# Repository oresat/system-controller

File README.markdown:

# OreSat "System Controller" Board 

## Overview

TBD

## Description

TBD

## Notes

TBD

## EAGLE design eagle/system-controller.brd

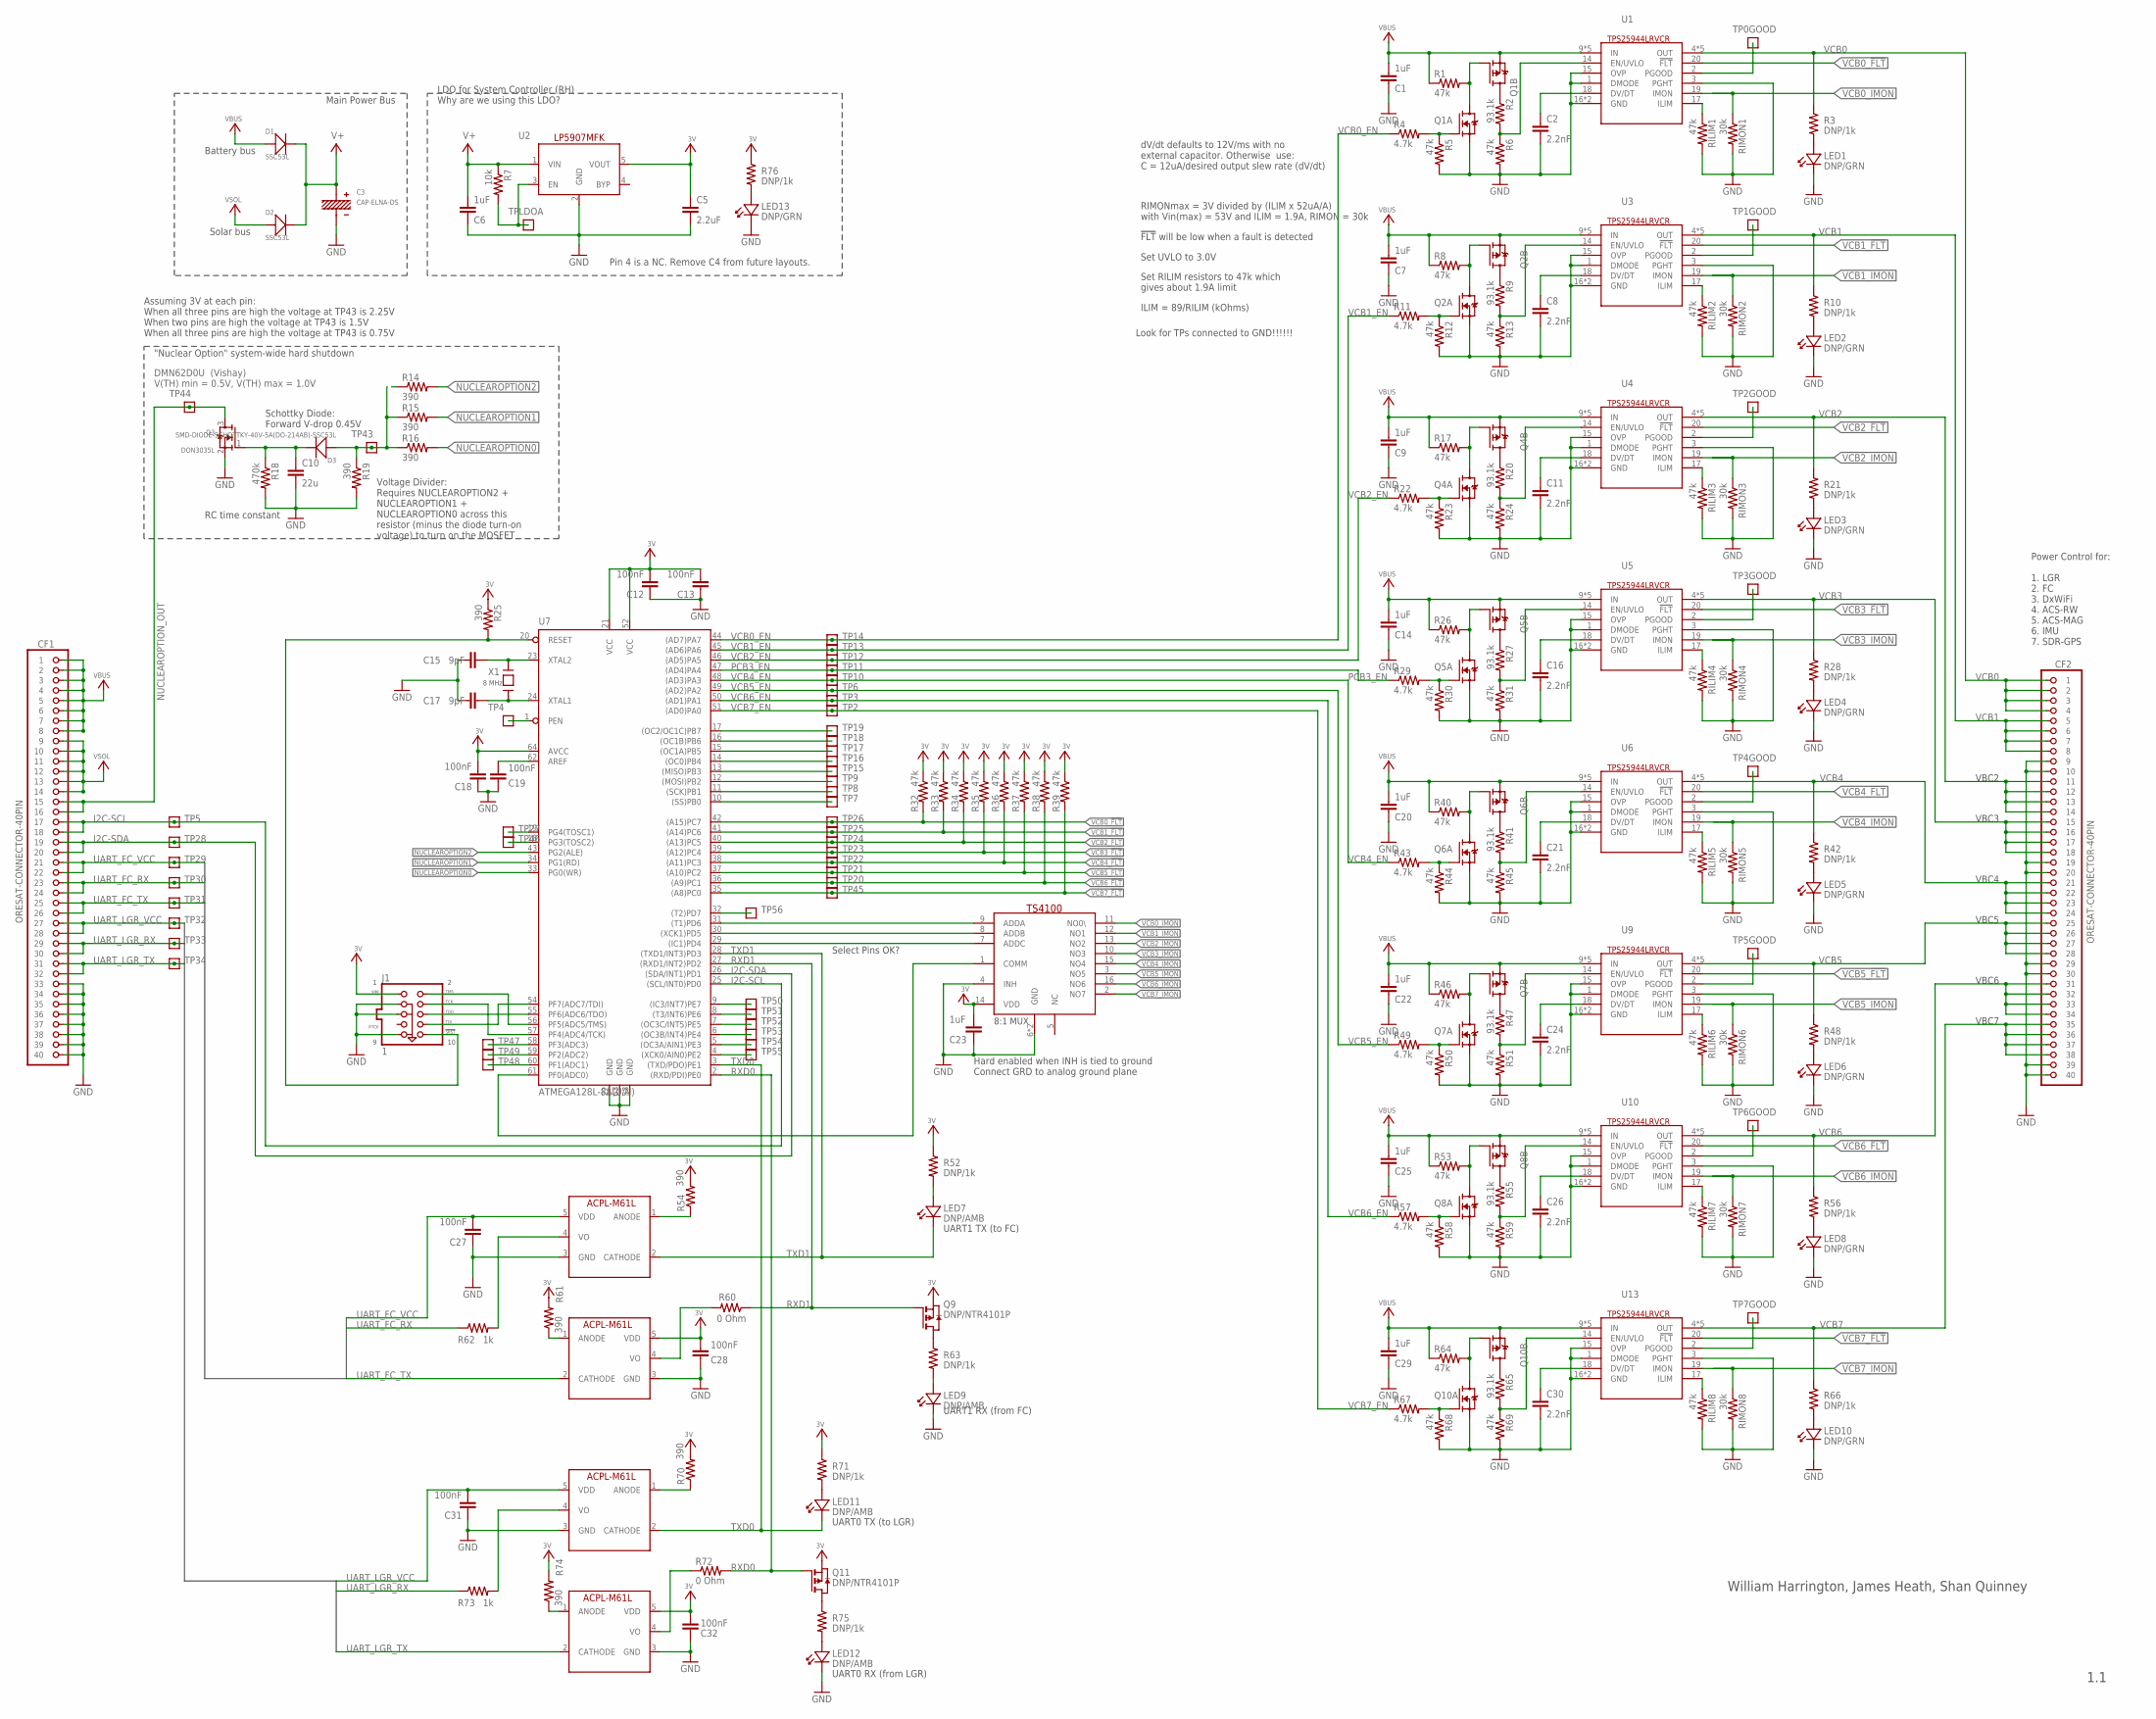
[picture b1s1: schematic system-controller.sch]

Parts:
C1, C6, C7, C9, C14, C20, C22, C23, C25, C29: 1uF; .0603-B-NOSILK; MPN CL10B105KP8NNNC
C2, C8, C11, C16, C21, C24, C26, C30: 2.2nF; .0603-B-NOSILK; MPN CL10C222GA8NNNC
C3: CAP-ELNA-DS; CAP-ELNA-DS-SERIES; MPN DSK-3R3H224U-HL
C5: 2.2uF; .0603-B-NOSILK; MPN CL10A225KQ8NNNC
C10: 22u; .0603-B-NOSILK; MPN C0603C103J5RACTU
C12, C13, C18, C19, C27, C28: 100nF; .0603-B-NOSILK; MPN C0603C104J4RACTU
C15, C17: 9pF; .0603-B-NOSILK; MPN CBR02C909B5GAC
C31, C32: 100nF; .0603-B-NOSILK; MPN GRM155R71C104JA88D
CF1, CF2: ORESAT-CONNECTOR-40PIN; HARWIN-ARCHER-M50-3202045; MPN M50-3202045
D1, D2: SSC53L; DO-214AB; MPN SSC53L-E3/57T
D3: SMD-DIODE-SCHOTTKY-40V-5A(DO-214AB)-SSC53L; DO-214AB; MPN SSC53L-E3/57T
J1: 1; PINHEADER-2X5-0.05+POL+SILK; MPN 3220-10-0100-00
LED1, LED2, LED3, LED4, LED5, LED6, LED8, LED10, LED13: DNP/GRN; LED-0603; MPN 150060GS75000
LED7, LED9, LED11, LED12: DNP/AMB; LED-0603; MPN LA L296-Q2R2-1-Z
Q1, Q2, Q4, Q5, Q6, Q7, Q8, Q10: MOSFET-P-N-PAIR; SOT23-6; MPN DMG6601LVT-7
Q3: DON3035L; SOT23; MPN DMN62D0U-13
Q9, Q11: DNP/NTR4101P; SOT23; MPN NTR4101PT1H
R1, R5, R6, R8, R12, R13, R17, R23, R24, R26, R30, R31, R32, R33, R34, R35, R36, R37, R38, R39, R40, R44, R45, R46, R50, R51, R53, R58, R59, R64, R68, R69: 47k; .0603-B-NOSILK; MPN RC1608F473CS
R2, R9, R20, R27, R41, R47, R55, R65: 93.1k; .0603-B-NOSILK; MPN RC1608F9312CS
R3, R10, R21, R28, R42, R48, R52, R56, R63, R66, R71, R75, R76: DNP/1k; .0603-B-NOSILK; MPN RC1608F102CS
R4, R11, R22, R29, R43, R49, R57, R67: 4.7k; .0603-B-NOSILK; MPN RC1608F472CS
R7: 10k; .0603-B-NOSILK; MPN RC1608F103CS
R14, R15, R16, R19, R25, R54, R61, R70, R74: 390; .0603-B-NOSILK; MPN 4-1676481-5
R18: 470k; .0603-B-NOSILK; MPN RC1608F474CS
R60, R72: 0 Ohm; .0603-B-NOSILK; MPN 4-1676481-5
R62, R73: 1k; .0603-B-NOSILK; MPN 4-1676481-5
RILIM1, RILIM2, RILIM3, RILIM4, RILIM5, RILIM6, RILIM7, RILIM8: 47k; .0603-B-NOSILK; MPN RC1608F473CS
RIMON1, RIMON2, RIMON3, RIMON4, RIMON5, RIMON6, RIMON7, RIMON8: 30k; .0603-B-NOSILK; MPN RC1608F3012CS
TP0GOOD, TP1GOOD, TP2, TP2GOOD, TP3, TP3GOOD, TP4, TP4GOOD, TP5, TP5GOOD, TP6, TP6GOOD, TP7, TP7GOOD, TP8, TP9, TP10, TP11, TP12, TP13, TP14, TP15, TP16, TP17, TP18, TP19, TP20, TP21, TP22, TP23, TP24, TP25, TP26, TP27, TP28, TP29, TP30, TP31, TP32, TP33, TP34, TP43, TP44, TP45, TP46, TP47, TP48, TP49, TP50, TP51, TP52, TP53, TP54, TP55, TP56: TEST-POINT; 2MM-TEST-POINT
TPLDOA: TEST-POINT; 2MM-TEST-POINT
U1, U3, U4, U5, U6, U9, U10, U13: TPS25944LRVCRWQFN-20-3X4; QFN-20-L; MPN TPS25944LRVCR
U2: LP5907MFX-3.0; SOT-23; MPN LP5907MFX-3.0/NOPB
U7: ATMEGA128L-8A(U/N); TQFP64
U8: TS4100; QFN50P400X400X80-17N; MPN TS4100ITQ1633
U$1, U$2, U$3, U$4: ACPL-M61L
X1: 8 MHz CRYSTAL-ABRACON-ABM3-SMD; CRYSTAL-ABRACON-ABM3-SMD; MPN Abracon LLC

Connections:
3V: C5.1, C12.2, C13.2, C18.2, C23.2, C28.2, C32.2, J1.1 (VDD), Q9.2 (S), Q11.2 (S), R25.1, R32.1, R33.1, R34.1, R35.1, R36.1, R37.1, R38.1, R39.1, R52.1, R54.2, R61.2, R70.2, R71.1, R74.2, R76.1, U2.5 (VOUT), U7.21 (VCC), U7.52 (VCC), U7.64 (AVCC), U8.14 (VDD), U$3.5 (VDD), U$4.5 (VDD)
AREF: C19.2, U7.62 (AREF)
GND: C1.1, C2.2, C3.-, C5.2, C6.1, C7.1, C8.2, C9.1, C10.2, C11.2, C12.1, C13.1, C14.1, C15.1, C16.2, C17.1, C18.1, C19.1, C20.1, C21.2, C22.1, C23.1, C24.2, C25.1, C26.2, C27.1, C28.1, C29.1, C30.2, C31.1, C32.1, CF1.P$33 (33), CF1.P$34 (34), CF1.P$35 (35), CF1.P$36 (36), CF1.P$37 (37), CF1.P$38 (38), CF1.P$39 (39), CF1.P$40 (40), CF2.P$9 (9), CF2.P$10 (10), CF2.P$19 (19), CF2.P$20 (20), CF2.P$29 (29), CF2.P$30 (30), CF2.P$39 (39), CF2.P$40 (40), J1.3 (GND3), J1.5 (GND5), J1.9 (GND9), LED1.K, LED2.K, LED3.K, LED4.K, LED5.K, LED6.K, LED8.K, LED9.K, LED10.K, LED12.K, LED13.K, Q1.5 (S), Q2.5 (S), Q3.2 (S), Q4.5 (S), Q5.5 (S), Q6.5 (S), Q7.5 (S), Q8.5 (S), Q10.5 (S), R5.2, R6.2, R12.2, R13.2, R18.2, R19.2, R23.2, R24.2, R30.2, R31.2, R44.2, R45.2, R50.2, R51.2, R58.2, R59.2, R68.2, R69.2, RILIM1.2, RILIM2.2, RILIM3.2, RILIM4.2, RILIM5.2, RILIM6.2, RILIM7.2, RILIM8.2, RIMON1.2, RIMON2.2, RIMON3.2, RIMON4.2, RIMON5.2, RIMON6.2, RIMON7.2, RIMON8.2, U1.1 (DMODE), U1.3 (PGHT), U1.15 (OVP), U1.16 (GND), U1.21 (GND), U2.2 (GND), U3.1 (DMODE), U3.3 (PGHT), U3.15 (OVP), U3.16 (GND), U3.21 (GND), U4.1 (DMODE), U4.3 (PGHT), U4.15 (OVP), U4.16 (GND), U4.21 (GND), U5.1 (DMODE), U5.3 (PGHT), U5.15 (OVP), U5.16 (GND), U5.21 (GND), U6.1 (DMODE), U6.3 (PGHT), U6.15 (OVP), U6.16 (GND), U6.21 (GND), U7.22 (GND), U7.53 (GND), U7.63 (GND), U8.4 (INH), U8.6 (GND), U8.17 (GND), U9.1 (DMODE), U9.3 (PGHT), U9.15 (OVP), U9.16 (GND), U9.21 (GND), U10.1 (DMODE), U10.3 (PGHT), U10.15 (OVP), U10.16 (GND), U10.21 (GND), U13.1 (DMODE), U13.3 (PGHT), U13.15 (OVP), U13.16 (GND), U13.21 (GND), U$1.3 (GND), U$2.3 (GND), U$3.3 (GND), U$4.3 (GND)
I2C-SCL: CF1.P$17 (17), CF1.P$18 (18), TP5.1, U7.25 ((SCL/INT0)PD0)
I2C-SDA: CF1.P$19 (19), CF1.P$20 (20), TP28.1, U7.26 ((SDA/INT1)PD1)
INOF: C2.1, U1.18 (DV/DT)
unnamed: C17.2, U7.24 (XTAL1), X1.P$2
unnamed: Q2.4 (D), R9.1
unnamed: R70.1, U$2.1 (ANODE)
unnamed: R62.2, U$1.4 (VO)
unnamed: LED13.A, R76.2
unnamed: R61.1, U$3.1 (ANODE)
unnamed: R2.2, R6.1, U1.14 (EN/UVLO)
unnamed: R20.2, R24.1, U4.14 (EN/UVLO)
unnamed: J1.4 (TCK), U7.57 (PF4(ADC4/TCK))
unnamed: J1.6 (TDO), U7.55 (PF6(ADC6/TDO))
unnamed: J1.8 (TDI), U7.54 (PF7(ADC7/TDI))
unnamed: J1.2 (TMS), U7.56 (PF5(ADC5/TMS))
unnamed: J1.10 (SRST), R25.2, U7.20 (RESET)
unnamed: R73.2, U$2.4 (VO)
unnamed: C15.2, U7.23 (XTAL2), X1.P$1
unnamed: R72.1, U$4.4 (VO)
unnamed: RILIM3.1, U4.17 (ILIM)
unnamed: RILIM1.1, U1.17 (ILIM)
unnamed: R7.2, TPLDOA.1, U2.3 (EN)
unnamed: R60.2, U$3.4 (VO)
unnamed: TP0GOOD.1, U1.2 (PGOOD)
unnamed: LED1.A, R3.2
unnamed: TP46.1, U7.18 (PG3(TOSC2))
unnamed: TP27.1, U7.19 (PG4(TOSC1))
unnamed: R9.2, R13.1, U3.14 (EN/UVLO)
unnamed: RILIM2.1, U3.17 (ILIM)
unnamed: TP1GOOD.1, U3.2 (PGOOD)
unnamed: TP4.1, U7.1 (PEN)
unnamed: TP47.1, U7.58 (PF3(ADC3))
unnamed: TP49.1, U7.59 (PF2(ADC2))
unnamed: TP48.1, U7.60 (PF1(ADC1))
unnamed: C8.1, U3.18 (DV/DT)
unnamed: TP55.1, U7.4 ((XCK0/AIN0)PE2)
unnamed: TP54.1, U7.5 ((OC3A/AIN1)PE3)
unnamed: TP53.1, U7.6 ((OC3B/INT4)PE4)
unnamed: TP52.1, U7.7 ((OC3C/INT5)PE5)
unnamed: TP51.1, U7.8 ((T3/INT6)PE6)
unnamed: TP50.1, U7.9 ((IC3/INT7)PE7)
unnamed: LED2.A, R10.2
unnamed: U7.29 ((IC1)PD4), U8.7 (ADDC)
unnamed: U7.30 ((XCK1)PD5), U8.8 (ADDB)
unnamed: U7.31 ((T1)PD6), U8.9 (ADDA)
unnamed: Q2.1 (G), R11.2, R12.1
unnamed: Q1.1 (G), R4.2, R5.1
unnamed: Q2.3 (G), Q2.6 (D), R8.2
unnamed: LED3.A, R21.2
unnamed: LED12.A, R75.2
unnamed: R74.1, U$4.1 (ANODE)
unnamed: Q11.3 (D), R75.1
unnamed: LED7.A, R52.2
unnamed: LED11.A, R71.2
unnamed: R54.1, U$1.1 (ANODE)
unnamed: TP2GOOD.1, U4.2 (PGOOD)
unnamed: LED9.A, R63.2
unnamed: Q9.3 (D), R63.1
unnamed: C11.1, U4.18 (DV/DT)
unnamed: Q4.1 (G), R22.2, R23.1
unnamed: Q4.4 (D), R20.1
unnamed: Q4.3 (G), Q4.6 (D), R17.2
unnamed: LED4.A, R28.2
unnamed: R65.2, R69.1, U13.14 (EN/UVLO)
unnamed: RILIM8.1, U13.17 (ILIM)
unnamed: TP7GOOD.1, U13.2 (PGOOD)
unnamed: C30.1, U13.18 (DV/DT)
unnamed: Q10.1 (G), R67.2, R68.1
unnamed: Q1.3 (G), Q1.6 (D), R1.2
unnamed: Q10.3 (G), Q10.6 (D), R64.2
unnamed: LED5.A, R42.2
unnamed: R47.2, R51.1, U9.14 (EN/UVLO)
unnamed: RILIM6.1, U9.17 (ILIM)
unnamed: TP5GOOD.1, U9.2 (PGOOD)
unnamed: C24.1, U9.18 (DV/DT)
unnamed: Q7.1 (G), R49.2, R50.1
unnamed: Q1.4 (D), R2.1
unnamed: Q7.3 (G), Q7.6 (D), R46.2
unnamed: LED6.A, R48.2
unnamed: R41.2, R45.1, U6.14 (EN/UVLO)
unnamed: RILIM5.1, U6.17 (ILIM)
unnamed: TP4GOOD.1, U6.2 (PGOOD)
unnamed: C21.1, U6.18 (DV/DT)
unnamed: Q6.1 (G), R43.2, R44.1
unnamed: Q5.4 (D), R27.1
unnamed: Q6.3 (G), Q6.6 (D), R40.2
unnamed: LED8.A, R56.2
unnamed: R27.2, R31.1, U5.14 (EN/UVLO)
unnamed: RILIM4.1, U5.17 (ILIM)
unnamed: TP3GOOD.1, U5.2 (PGOOD)
unnamed: C16.1, U5.18 (DV/DT)
unnamed: Q5.1 (G), R29.2, R30.1
unnamed: Q6.4 (D), R41.1
unnamed: Q5.3 (G), Q5.6 (D), R26.2
unnamed: LED10.A, R66.2
unnamed: R55.2, R59.1, U10.14 (EN/UVLO)
unnamed: RILIM7.1, U10.17 (ILIM)
unnamed: TP6GOOD.1, U10.2 (PGOOD)
unnamed: C26.1, U10.18 (DV/DT)
unnamed: Q8.1 (G), R57.2, R58.1
unnamed: TP56.1, U7.32 ((T2)PD7)
unnamed: Q8.3 (G), Q8.6 (D), R53.2
unnamed: C10.1, D3.2 (-), Q3.1 (G), R18.1
unnamed: U7.61 (PF0(ADC0)), U8.1 (COMM)
unnamed: Q7.4 (D), R47.1
unnamed: D3.1 (+), R14.1, R15.1, R16.1, R19.1, TP43.1
unnamed: Q10.4 (D), R65.1
unnamed: Q8.4 (D), R55.1
NUCLEAROPTION0: R16.2, U7.33 (PG0(WR))
NUCLEAROPTION1: R15.2, U7.34 (PG1(RD))
NUCLEAROPTION2: R14.2, U7.43 (PG2(ALE))
NUCLEAROPTION_OUT: CF1.P$15 (15), CF1.P$16 (16), Q3.3 (D), TP44.1
PB0: TP7.1, U7.10 ((SS)PB0)
PB1: TP8.1, U7.11 ((SCK)PB1)
PB2: TP9.1, U7.12 ((MOSI)PB2)
PB3: TP15.1, U7.13 ((MISO)PB3)
PB4: TP16.1, U7.14 ((OC0)PB4)
PB5: TP17.1, U7.15 ((OC1A)PB5)
PB6: TP18.1, U7.16 ((OC1B)PB6)
PB7: TP19.1, U7.17 ((OC2/OC1C)PB7)
PCB3_EN: R29.1, TP11.1, U7.47 ((AD4)PA4)
RXD0: Q11.1 (G), R72.2, U7.2 ((RXD/PDI)PE0)
RXD1: Q9.1 (G), R60.1, U7.27 ((RXD1/INT2)PD2)
TXD0: LED11.K, U7.3 ((TXD/PDO)PE1), U$2.2 (CATHODE)
TXD1: LED7.K, U7.28 ((TXD1/INT3)PD3), U$1.2 (CATHODE)
UART_FC_RX: CF1.P$23 (23), CF1.P$24 (24), R62.1, TP30.1
UART_FC_TX: CF1.P$25 (25), CF1.P$26 (26), TP31.1, U$3.2 (CATHODE)
UART_FC_VCC: C27.2, CF1.P$21 (21), CF1.P$22 (22), TP29.1, U$1.5 (VDD)
UART_LGR_RX: CF1.P$29 (29), CF1.P$30 (30), R73.1, TP33.1
UART_LGR_TX: CF1.P$31 (31), CF1.P$32 (32), TP34.1, U$4.2 (CATHODE)
UART_LGR_VCC: C31.2, CF1.P$27 (27), CF1.P$28 (28), TP32.1, U$2.5 (VDD)
V+: C3.+, C6.2, D1.2 (-), D2.2 (-), R7.1, U2.1 (VIN)
VBUS: C1.2, C7.2, C9.2, C14.2, C20.2, C22.2, C25.2, C29.2, CF1.P$1 (1), CF1.P$2 (2), CF1.P$3 (3), CF1.P$4 (4), CF1.P$5 (5), CF1.P$6 (6), CF1.P$7 (7), CF1.P$8 (8), D1.1 (+), Q1.2 (S), Q2.2 (S), Q4.2 (S), Q5.2 (S), Q6.2 (S), Q7.2 (S), Q8.2 (S), Q10.2 (S), R1.1, R8.1, R17.1, R26.1, R40.1, R46.1, R53.1, R64.1, U1.9 (IN), U1.10 (IN), U1.11 (IN), U1.12 (IN), U1.13 (IN), U3.9 (IN), U3.10 (IN), U3.11 (IN), U3.12 (IN), U3.13 (IN), U4.9 (IN), U4.10 (IN), U4.11 (IN), U4.12 (IN), U4.13 (IN), U5.9 (IN), U5.10 (IN), U5.11 (IN), U5.12 (IN), U5.13 (IN), U6.9 (IN), U6.10 (IN), U6.11 (IN), U6.12 (IN), U6.13 (IN), U9.9 (IN), U9.10 (IN), U9.11 (IN), U9.12 (IN), U9.13 (IN), U10.9 (IN), U10.10 (IN), U10.11 (IN), U10.12 (IN), U10.13 (IN), U13.9 (IN), U13.10 (IN), U13.11 (IN), U13.12 (IN), U13.13 (IN)
VCB0: CF2.P$1 (1), CF2.P$2 (2), CF2.P$3 (3), CF2.P$4 (4), R3.1, U1.4 (OUT), U1.5 (OUT), U1.6 (OUT), U1.7 (OUT), U1.8 (OUT)
VCB0_!FLT: R32.2, TP26.1, U1.20 (!FLT), U7.42 ((A15)PC7)
VCB0_EN: R4.1, TP14.1, U7.44 ((AD7)PA7)
VCB0_IMON: RIMON1.1, U1.19 (IMON), U8.11 (NO0\)
VCB1: CF2.P$5 (5), CF2.P$6 (6), CF2.P$7 (7), CF2.P$8 (8), R10.1, U3.4 (OUT), U3.5 (OUT), U3.6 (OUT), U3.7 (OUT), U3.8 (OUT)
VCB1_!FLT: R33.2, TP25.1, U3.20 (!FLT), U7.41 ((A14)PC6)
VCB1_EN: R11.1, TP13.1, U7.45 ((AD6)PA6)
VCB1_IMON: RIMON2.1, U3.19 (IMON), U8.12 (NO1)
VCB2: CF2.P$11 (11), CF2.P$12 (12), CF2.P$13 (13), CF2.P$14 (14), R21.1, U4.4 (OUT), U4.5 (OUT), U4.6 (OUT), U4.7 (OUT), U4.8 (OUT)
VCB2_!FLT: R34.2, TP24.1, U4.20 (!FLT), U7.40 ((A13)PC5)
VCB2_EN: R22.1, TP12.1, U7.46 ((AD5)PA5)
VCB2_IMON: RIMON3.1, U4.19 (IMON), U8.13 (NO2)
VCB3: CF2.P$15 (15), CF2.P$16 (16), CF2.P$17 (17), CF2.P$18 (18), R28.1, U5.4 (OUT), U5.5 (OUT), U5.6 (OUT), U5.7 (OUT), U5.8 (OUT)
VCB3_!FLT: R35.2, TP23.1, U5.20 (!FLT), U7.39 ((A12)PC4)
VCB3_IMON: RIMON4.1, U5.19 (IMON), U8.10 (NO3)
VCB4: CF2.P$21 (21), CF2.P$22 (22), CF2.P$23 (23), CF2.P$24 (24), R42.1, U6.4 (OUT), U6.5 (OUT), U6.6 (OUT), U6.7 (OUT), U6.8 (OUT)
VCB4_!FLT: R36.2, TP22.1, U6.20 (!FLT), U7.38 ((A11)PC3)
VCB4_EN: R43.1, TP10.1, U7.48 ((AD3)PA3)
VCB4_IMON: RIMON5.1, U6.19 (IMON), U8.15 (NO4)
VCB5: CF2.P$25 (25), CF2.P$26 (26), CF2.P$27 (27), CF2.P$28 (28), R48.1, U9.4 (OUT), U9.5 (OUT), U9.6 (OUT), U9.7 (OUT), U9.8 (OUT)
VCB5_!FLT: R37.2, TP21.1, U7.37 ((A10)PC2), U9.20 (!FLT)
VCB5_EN: R49.1, TP6.1, U7.49 ((AD2)PA2)
VCB5_IMON: RIMON6.1, U8.3 (NO5), U9.19 (IMON)
VCB6: CF2.P$31 (31), CF2.P$32 (32), CF2.P$33 (33), CF2.P$34 (34), R56.1, U10.4 (OUT), U10.5 (OUT), U10.6 (OUT), U10.7 (OUT), U10.8 (OUT)
VCB6_!FLT: R38.2, TP20.1, U7.36 ((A9)PC1), U10.20 (!FLT)
VCB6_EN: R57.1, TP3.1, U7.50 ((AD1)PA1)
VCB6_IMON: RIMON7.1, U8.16 (NO6), U10.19 (IMON)
VCB7: CF2.P$35 (35), CF2.P$36 (36), CF2.P$37 (37), CF2.P$38 (38), R66.1, U13.4 (OUT), U13.5 (OUT), U13.6 (OUT), U13.7 (OUT), U13.8 (OUT)
VCB7_!FLT: R39.2, TP45.1, U7.35 ((A8)PC0), U13.20 (!FLT)
VCB7_EN: R67.1, TP2.1, U7.51 ((AD0)PA0)
VCB7_IMON: RIMON8.1, U8.2 (NO7), U13.19 (IMON)
VSOL: CF1.P$9 (9), CF1.P$10 (10), CF1.P$11 (11), CF1.P$12 (12), CF1.P$13 (13), CF1.P$14 (14), D2.1 (+)

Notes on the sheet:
William Harrington, James Heath, Shan Quinney
LDO for System Controller (RH) Why are we using this LDO?
Main Power Bus
Battery bus
Solar bus
Power Control for: 1. LGR 2. FC 3. DxWiFi 4. ACS-RW 5. ACS-MAG 6. IMU 7. SDR-GPS
Set RILIM resistors to 47k which gives about 1.9A limit
dV/dt defaults to 12V/ms with no external capacitor. Otherwise use: C = 12uA/desired output slew rate (dV/dt)
RIMONmax = 3V divided by (ILIM x 52uA/A) with Vin(max) = 53V and ILIM = 1.9A, RIMON = 30k
ILIM = 89/RILIM (kOhms)
!FLT! will be low when a fault is detected
Set UVLO to 3.0V
UART0 TX (to LGR)
UART1 RX (from FC)
UART0 RX (from LGR)
UART1 TX (to FC)
VBC2
VBC3
VBC4
VBC5
VBC6
VBC7
Hard enabled when INH is tied to ground Connect GRD to analog ground plane
Select Pins OK?
"Nuclear Option" system-wide hard shutdown
Voltage Divider: Requires NUCLEAROPTION2 + NUCLEAROPTION1 + NUCLEAROPTION0 across this resistor (minus the diode turn-on voltage) to turn on the MOSFET
Schottky Diode: Forward V-drop 0.45V
RC time constant
8 MHz
DMN62D0U (Vishay) V(TH) min = 0.5V, V(TH) max = 1.0V
Assuming 3V at each pin: When all three pins are high the voltage at TP43 is 2.25V When two pins are high the voltage at TP43 is 1.5V When all three pins are high the voltage at TP43 is 0.75V
Look for TPs connected to GND!!!!!!
1.1
Pin 4 is a NC. Remove C4 from future layouts.

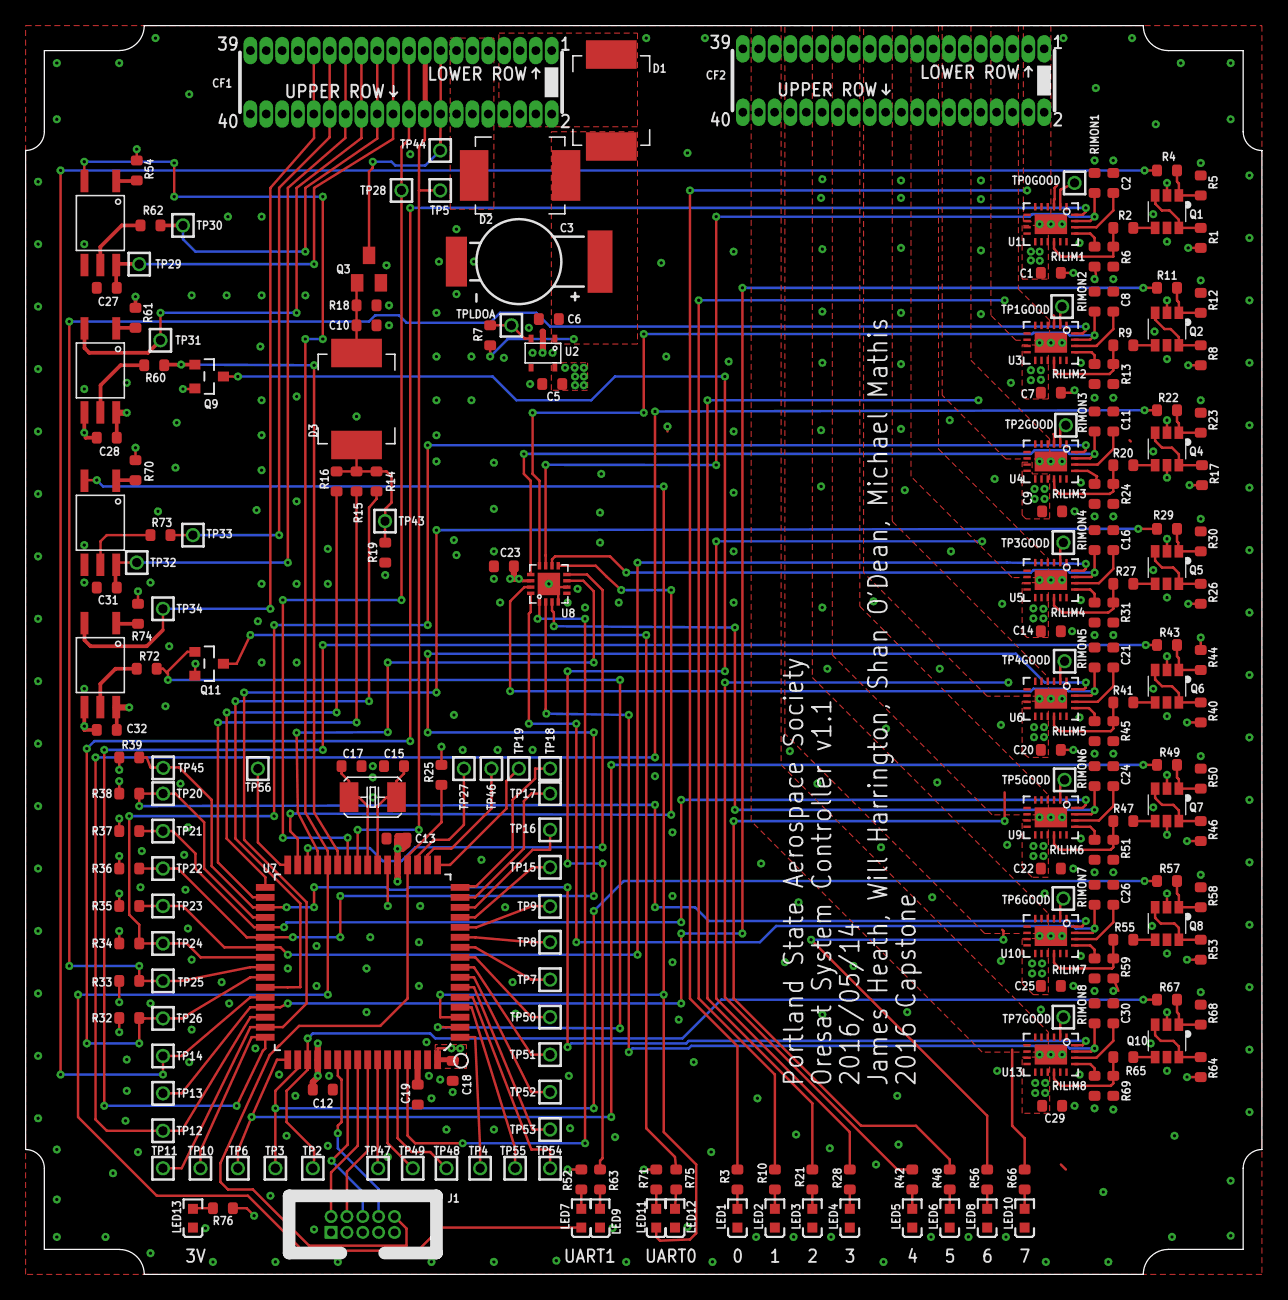
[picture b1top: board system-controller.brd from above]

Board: 4 copper layers, 99.0 x 100.0 mm, 226 parts (0 on the bottom side), 168 nets.

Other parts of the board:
U$5: ORESAT-CARD-V0.3

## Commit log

2016-02-27 Split schematic, added SPI cache symbol/fp, updated LL design
2016-02-28 Added GPIOs and other updates on SysCon sch. Updated SPI cache footprint
2016-02-28 Added super cap and LDO holding place
2016-02-28 Added LNA LDO footprint and circuitry
2016-02-28 Updated to do list
2016-02-29 Added rad-hard model LDO
2016-02-29 Fixed to do list
2016-03-01 Updated to do lists
2016-03-03 Added optocoupler datasheet and into the schematic
2016-03-03 added attributes, replaced atmega footprint with correct version, replaced resonator with xtal
2016-03-04 Got rid of SysCon LDO, fixed Optoisolator symbol
2016-03-05 Fixed OIs, fixed SysCon LDO, replaced SPI cache
2016-03-05 Had to fix to do again because I'm a dumbass
2016-03-19 Added the diodes and fixed the Crystal
2016-03-19 added headers to power supply
2016-03-23 Clean up on system controller board. Added 40 pin connector, board outline, ground planes. Killed all old spurious signals. Removed unecessary connectors. Still need to find small power controllers t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
2016-03-28 Newest outline of SC board, added secondary connector because we're going to need it for the output.
2016-04-01 Added the bare switch and deleted some text
2016-04-03 worked on the switch schematic
2016-04-03 A few more changes
2016-04-03 latest changes
2016-04-03 added a pull up resistor to FLT
2016-04-04 added the mux to the schematic
2016-04-04 added the updated mux to the schematic
2016-04-07 Added DNP LEDs and MOSFET drives to UARTs. Fixed TPS circuits with SOT-32-6 N/P MOSFET pair, which worked out nicely. Added another TPS to flesh it out, make sure it wasn't totally stupid. Added more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
2016-04-07 renamed boards
2016-04-07 created folder for firmware, added example code and makefile from old repo
2016-04-07 added readme for the firmware folder
2016-04-07 fixed typo
2016-04-07 revised readme for repo
2016-04-08 revised readme
2016-04-08 made changes to schematic: removed 16:1 mux, added 8:1 mux, configured remaining 8 eFuses, other
2016-04-09 added the remaining attribute info, fixed the footprint for the optoisolators
2016-04-10 Added a rough draft Hardware (analog) Watchdog circuit, added the voltage divider values for the UVLO pin on the eFuse
2016-04-10 added the MOSFET to the analog watchdog circuit
2016-04-10 Fixed nuclear option. Fixed ERCs. Found ERCs in ATMEGAS128, so broke that out of the default ATMEL library from CADSOFT and made our own (now in the oresat-eagle-libraries repo). Replaced test points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
2016-04-11 oh! yeah! datasheets
2016-04-12 added the remaining test points
2016-04-16 working on board layout. Have everything organized in in general location. Working on routing.
2016-04-18 Pushing newest changes to the board layout
2016-04-19 Design review with Shan and Andrew. Cleaned up polygons and polygon ranks. Used correct DRC rules.
2016-04-25 test file
2016-04-25 repo test
2016-04-25 Update test.md
    Split Parts Selection and added SC one here
2016-04-25 latetest changes pushed
2016-04-26 removed the duplicate readme that was blocking the original
2016-04-26 latest changes... thicker polys, moved some traces, more...
2016-04-26 added the RIMON resister value and dV/dt cap value
2016-04-26 latest minor changes
2016-04-27 made polygons wider and changed physical layout of them. Also, reduced space between traces
2016-04-27 latest updates added
2016-04-28 Update test.md
    Added Format note for reference.
2016-04-28 Initial sys controller firmware. Reset a countdown whenever a 'G' is received by the uart if a 'G' isn't received in time, the timer interrupt will run the reset_lgr routine
2016-04-29 newest changes
2016-04-29 Changed name of document so it makes sense
2016-04-29 Got rid of test.md
2016-04-30 final changes pushed for the day: change to optical isolation circuitry and board fixes due to this
2016-04-30 I lied. 1 more
2016-04-30 Update PartsSelection.md
    Made some updates. Finished up Atmel part, but still needs the reasons behind it. Worked on the opto-isolator part. A lot of these seem to be missing eagle reference numbers on the schematic and boar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
2016-04-30 Better layout for bypass caps ner AVR. Some cleanup on routing. Changed power domain indicators to DNP.
2016-05-03 Added echo to the uart receive so we can analyze it
2016-05-06 Added the BOM to the docs folder
2016-05-09 databook for atmegas128
2016-05-09 Made some additions to the PartSelection document and fixed some issues on the BOM
2016-05-09 A few more quick changes
2016-05-09 Added some comments to the firmware
2016-05-10 Some changes to the format of the PartsSelection doc and a few changes to the BOM
2016-05-10 tracking links
2016-05-10 More edditing of this document, yall
2016-05-10 Made some more edits to this document. Mostly correcting errors
2016-05-10 Changed the Radhard option so that it is closer to the LGR in formatting
2016-05-10 More edditing. Mostly making thic doc look more like the one in the LGR repo. For consistancy
2016-05-10 Board cleanup.
2016-05-10 Added names to missing parts and updated the BOM and Parts Selection doc accordingly
2016-05-11 More board cleanup!
2016-05-13 Lots of board cleanup. Improved packages for ATMEGA, analog switch, and TPS. Re-did power polygons to tighten up the layout. Straightened wires because OCD, fixed DRCs.
2016-05-14 Added 3V LED for power. Fixed a DRC error which wasn't caught earlier? How'd that happen? Also pushing gerbers, since some folks don't have EAGLE.
2016-05-15 atmega128 (non-radhard MCU) datasheet
2016-05-15 Added some info about the LDO
2016-05-17 More edits and additions to the parts selection document
2016-05-17 Remembered the caps and resistors
2016-05-17 Updating resitor and capacitor names
2016-05-17 added the 0 Ohm resistors R60 and R72
2016-05-17 Changed "Part" to "Description" and removed some of the excessive usage of colons.
2016-05-23 added missing datasheets
2016-05-23 renamed some folders in the datasheet folder
2016-05-23 deleting extra files
2016-05-23 another folder going byby
2016-06-01 added to the BOM
2016-06-08 Update README.md
    First change is copy and paste from the LGR
2016-06-08 Update README.md
    Added link to Parts Selection
2016-06-08 Update PartsSelection.md
    Removed "work in progress" at top of page
2016-06-08 Update README.md
    Added link to BOM
2016-06-08 Update README.md
    Added link to EagleCAD schematic
2016-06-08 Update README.md
    Added link to EagleCAD board layout
2016-06-08 Update README.md
    Added image of Oresat to SC block diagram
2016-06-08 Update README.md
    made an additional edit with the placement of the image in the Readme file
2016-06-08 Update README.md
    Added image of the SC board to the Readme file
2016-06-08 Update README.md
    change board image size to something more appropriate
2016-06-08 Update README.md
    resized image of board
2016-06-08 Update README.md
    A few more edits to center the image and move some text around
2016-06-08 Update README.md
    Changed the image size of the board again.
2016-06-08 Update README.md
    Using photo of board instead of illustration
2016-06-10 Fixed Low level image
2016-07-01 Update README.md
    Got rid of double image
2016-07-01 Update README.md
    Organization
2016-07-07 added license
2016-07-12 Fixed some of the remaining issues such as JTAG layout and schematic, 0 ohm resistors, etc. Check the issue section on the git for more info
2016-07-19 fixed reference designator and origin on optoisolator
2016-07-20 Fixed opto-isolator symbol with proper labels
2016-08-21 Refactoring system controller firmware
    1. Create toggle pin function meant for changing logic level on pin
    2. Created io direction setter function
    3. Replaced bit banging with calls to new functions (see above).
    4. F_CPU not set in util/delay.h see note in code
2016-08-22 More refactoring
    1. Created headers for hardware initialization functions
    2. Created implementation files to go with those headers
    3. Declared some enums and defines to make everything readable
    4. Added to makefile so they would compile
    5. Created efuse enum for USART0 RX ISR
    TODO: Address redefining AVR constants
2016-08-23 fixed logic in toggle_pin and set_io_direction functions
2016-09-03 i2c driver, fixed defines in adc, added adc and i2c to sys_control.c
2016-09-03 call to i2c_init added to sys_control.c, note that this code is untested but compiles
2016-09-04 implemented get_char, expanded uart driver to handle use of both modules, changed some constants for readability, added interrupt enable to init function
2016-09-05 Fixed Rad hard efuse document link
2016-09-06 corrected logic on argument checking in port functions
2016-12-07 1. Added boolean logic to init procedures for uart, adc, i2c 2. Created register bit manipulation helper functions with boolean logic 3. Added debugging constants 4. Added trap ability, organized by 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
2016-12-07 added debug to makefile object list
2016-12-11 1. Debugged lots of my new code that I committed prior 2. Added more debug infrastructure 3. Corrected mistakes in some init procedures 4. Made timer setup its own implementation and header file
2016-12-11 culled dead code, reidented files
2016-12-21 added print line function to uart driver
2017-02-10 added ADC testing stuff
